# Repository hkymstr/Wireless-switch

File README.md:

# Wireless Race Car Switch System — Hardware v2 (WiFi)

A fully wireless switch panel for a race car using two **Raspberry Pi Pico 2 W** boards.  
One board acts as the **Transmitter** (switch panel), the other as the **Receiver** (12 V output driver).

> **Bluetooth version:** see the `bluetooth` branch.

---

## System Overview

```
 ┌──────────────────────────┐      WiFi (AP/STA)      ┌─────────────────────────────┐
 │      TRANSMITTER         │ ◄──── UDP 20 Hz ──────► │        RECEIVER             │
 │    Raspberry Pi Pico 2W  │                          │    Raspberry Pi Pico 2W     │
 │                          │  Web UI: 192.168.4.1     │  Web UI: <RX-IP>            │
 │  GPIO 1-5 ← 5 switches   │                          │  GPIO 8-11 → 4× MOSFET     │
 │  GPIO 0  → Connected LED │                          │  GPIO 12   → Relay K2      │
 │  GPIO 7  → Searching LED │                          │  GPIO 0    → Connected LED  │
 │  Powered from 12 V via   │                          │  GPIO 7    → Searching LED  │
 │  on-board 5 V regulator  │                          │  Takes 12 V from car        │
 └──────────────────────────┘                          └─────────────────────────────┘
```

TX creates an **open WiFi access point** (`WirelessSwitch-1` by default). RX connects as a station.  
Both boards host a **web settings page** — join the WiFi network and open a browser to configure.

---

## Web Interface

| Board | URL | What you can change |
|-------|-----|---------------------|
| TX | `http://192.168.4.1` | Pair ID |
| RX | `http://<RX-IP>` (linked from TX page) | Pair ID, hold time, channel modes |

Connect any phone or laptop to the `WirelessSwitch-N` WiFi network (no password), then open the URL above. Settings are saved to flash and survive power cycles.

---

## GPIO Pin Mapping — Hardware v2

### Status LEDs (identical on both boards)

| GPIO | Function      | Behaviour                                     |
|------|---------------|-----------------------------------------------|
|  0   | CONNECTED LED | Solid ON when wireless link is up             |
|  7   | SEARCHING LED | Flashes 2 Hz while searching; OFF when linked |

### Transmitter — Switch Inputs

Switches are **active-low** (connect switch between GPIO pin and GND).  
Internal pull-ups enabled in firmware.

| GPIO | Channel | Description    |
|------|---------|----------------|
|  1   | SW1     | Switch 1 input |
|  2   | SW2     | Switch 2 input |
|  3   | SW3     | Switch 3 input |
|  4   | SW4     | Switch 4 input |
|  5   | SW5     | Switch 5 input |

### Receiver — Output Channels

Outputs are **active-high** (GPIO HIGH = output energised).

| GPIO | Channel | Type            | Max Load         |
|------|---------|-----------------|------------------|
|  8   | CH1     | N-ch MOSFET     | 5 A @ 12 V       |
|  9   | CH2     | N-ch MOSFET     | 5 A @ 12 V       |
| 10   | CH3     | N-ch MOSFET     | 5 A @ 12 V       |
| 11   | CH4     | N-ch MOSFET     | 5 A @ 12 V       |
| 12   | CH5     | Relay K2 (SPDT) | Per relay rating |

---

## Repository Structure

```
├── kicad/
│   ├── wireless_switch.kicad_pro   KiCad project file
│   ├── wireless_switch.kicad_sch   Top-level schematic
│   ├── Pico_interface.kicad_sch    Pico 2 W GPIO interface sub-sheet
│   ├── analog_in.kicad_sch         Output channel sub-sheet (MOSFET + relay)
│   ├── input_power.kicad_sch       12 V → 5 V power supply sub-sheet
│   ├── wireless_switch.kicad_pcb   PCB layout
│   └── sym-lib-table               KiCad symbol library table
│
├── firmware/
│   ├── config.py        Shared configuration (defaults – overridden by web UI)
│   ├── tx_main.py       Transmitter MicroPython firmware
│   ├── rx_main.py       Receiver MicroPython firmware
│   ├── install_tx.bat   Windows transmitter installer  (default COM3)
│   ├── install_rx.bat   Windows receiver installer     (default COM5)
│   ├── install_tx.sh    Linux / macOS transmitter installer
│   ├── install_rx.sh    Linux / macOS receiver installer
│   ├── verify.bat       18-point verification script (Windows)
│   ├── led_test.bat     LED blink test (Windows)
│   └── polarity_test.bat  LED polarity / GPIO finder (Windows)
│
└── docs/
    └── wireless_switch.pdf   Full schematic PDF
```

---

## Hardware Requirements

### Per Board (× 2)
- Raspberry Pi Pico 2 W
- PCB from `kicad/wireless_switch.kicad_pcb`

### Transmitter PCB BOM additions
- 5× panel-mount toggle switches (SPDT or SPST)
- 2× LEDs with 330 Ω series resistors for GPIO 0 & 7
- 12 V → 5 V onboard regulator + capacitors (see `input_power.kicad_sch`)

### Receiver PCB BOM additions
- 4× N-channel logic-level MOSFETs (e.g. IRLZ44N) with gate resistors
- 1× 12 V SPDT relay K2 (Omron G5V-1 or equivalent)
- Relay driver transistor + flyback diodes
- Fusing on each output channel

---

## Software Installation

### Step 1 — Flash MicroPython to each Pico 2 W

1. Download the **Pico 2 W** MicroPython UF2 from  
   `https://micropython.org/download/RPI_PICO2_W/`
2. Hold **BOOTSEL**, plug USB → Pico appears as `RPI-RP2` mass storage
3. Drag the `.uf2` onto the drive — Pico reboots automatically

### Step 2 — Install `mpremote`

```bash
pip install mpremote
```

### Step 3 — Install Transmitter firmware

**Windows** (default COM3):
```bat
cd firmware
install_tx.bat
install_tx.bat COM4    ← specify a different port if needed
```

**Linux / macOS:**
```bash
cd firmware
chmod +x install_tx.sh && ./install_tx.sh
```

Confirm: board blinks SEARCHING LED **3× quickly** then flashes slowly.

### Step 4 — Install Receiver firmware

**Windows** (default COM5):
```bat
install_rx.bat
```

**Linux / macOS:**
```bash
./install_rx.sh
```

### Step 5 — Verify (optional, Windows)

```bat
verify.bat COM3 COM5
led_test.bat COM3 COM5
```

---

## Operation

1. **Power on both boards.** Both blink the SEARCHING LED **3× quickly** to confirm firmware is running.
2. TX creates an open WiFi access point. Both boards flash their SEARCHING LED while waiting for a link.
3. Once linked, **CONNECTED LED turns solid** on both boards; SEARCHING LED turns off.
4. Pressing a switch on TX activates the corresponding output on RX according to that channel's mode.
5. **On link loss:** RX holds its last output states for the configured hold time (default 10 s), then turns all outputs off. Both boards resume searching.

### Link Parameters

| Parameter           | Value                  |
|---------------------|------------------------|
| Update rate         | 20 Hz (every 50 ms)    |
| Link timeout        | 2 s                    |
| Hold on disconnect  | 10 s (configurable)    |
| Protocol            | UDP port 4210          |
| WiFi mode           | TX = AP, RX = Station  |
| Network             | Open (no password)     |

---

## Channel Modes

Each output channel can be set independently via the RX web interface:

| Mode      | Behaviour                                            |
|-----------|------------------------------------------------------|
| Momentary | Output ON while switch is held; OFF when released    |
| Latch     | First press turns output ON; next press turns it OFF |

Latch state is preserved through brief disconnects (within hold window).  
A disconnection longer than the hold time resets all latch states to OFF.

---

## Multiple Pairs

If two TX/RX pairs operate at the same time, each pair needs a unique **Pair ID** so they don't cross-connect.

Set the same Pair ID on both boards in a pair via the web interface:

| Pair | TX SSID         | RX connects to  |
|------|-----------------|-----------------|
|  1   | WirelessSwitch-1 | WirelessSwitch-1 |
|  2   | WirelessSwitch-2 | WirelessSwitch-2 |

**Procedure for changing Pair ID:**
1. Connect to the current WiFi network
2. Open RX settings → change Pair ID → Save (RX reboots, now looks for new SSID)
3. Open TX settings (192.168.4.1) → change Pair ID → Save (TX reboots with new SSID)
4. RX reconnects automatically

---

## Troubleshooting

| Symptom | Likely cause | Fix |
|---------|--------------|-----|
| No 3× startup blink | Firmware not installed | Re-run the installer; verify MicroPython UF2 was flashed first |
| SEARCHING LED never stops flashing | Wrong Pair ID or TX not powered | Check both boards have the same Pair ID; confirm TX SEARCHING LED is also flashing |
| TX AP has stale WPA2 password | Old security settings cached in chip | Firmware resets the AP before configuring — power-cycle TX |
| Can't open web interface | Not connected to WirelessSwitch-N WiFi | Join the WiFi network first (no password), then open the URL |
| RX web page not reachable | RX IP unknown | Open TX page (192.168.4.1) first — it shows a clickable link to the RX page |
| Outputs don't activate | Wrong firmware on board | Confirm TX has `tx_main.py` installed as `main.py` |
| Latch output stuck after reboot | Expected — latch state is in RAM only | Press the switch once to toggle off |
| `mpremote` cannot find device | Driver missing or wrong port | Run `python -m mpremote connect list` |
| Pico not detected as storage | Not holding BOOTSEL | Hold BOOTSEL before plugging USB |

---

## Protocol Reference

UDP packet format (7 bytes, TX → RX, port 4210):

```
Byte 0   : 0xAA  (start marker)
Byte 1   : Switch 1 state  (0 = open, 1 = pressed)
Byte 2   : Switch 2 state
Byte 3   : Switch 3 state
Byte 4   : Switch 4 state
Byte 5   : Switch 5 state
Byte 6   : Checksum  = (SW1+SW2+SW3+SW4+SW5) & 0xFF
```

RX → TX heartbeat: `b"RXHERE"` (6 bytes, every 50 ms) — tells TX the RX's IP address.

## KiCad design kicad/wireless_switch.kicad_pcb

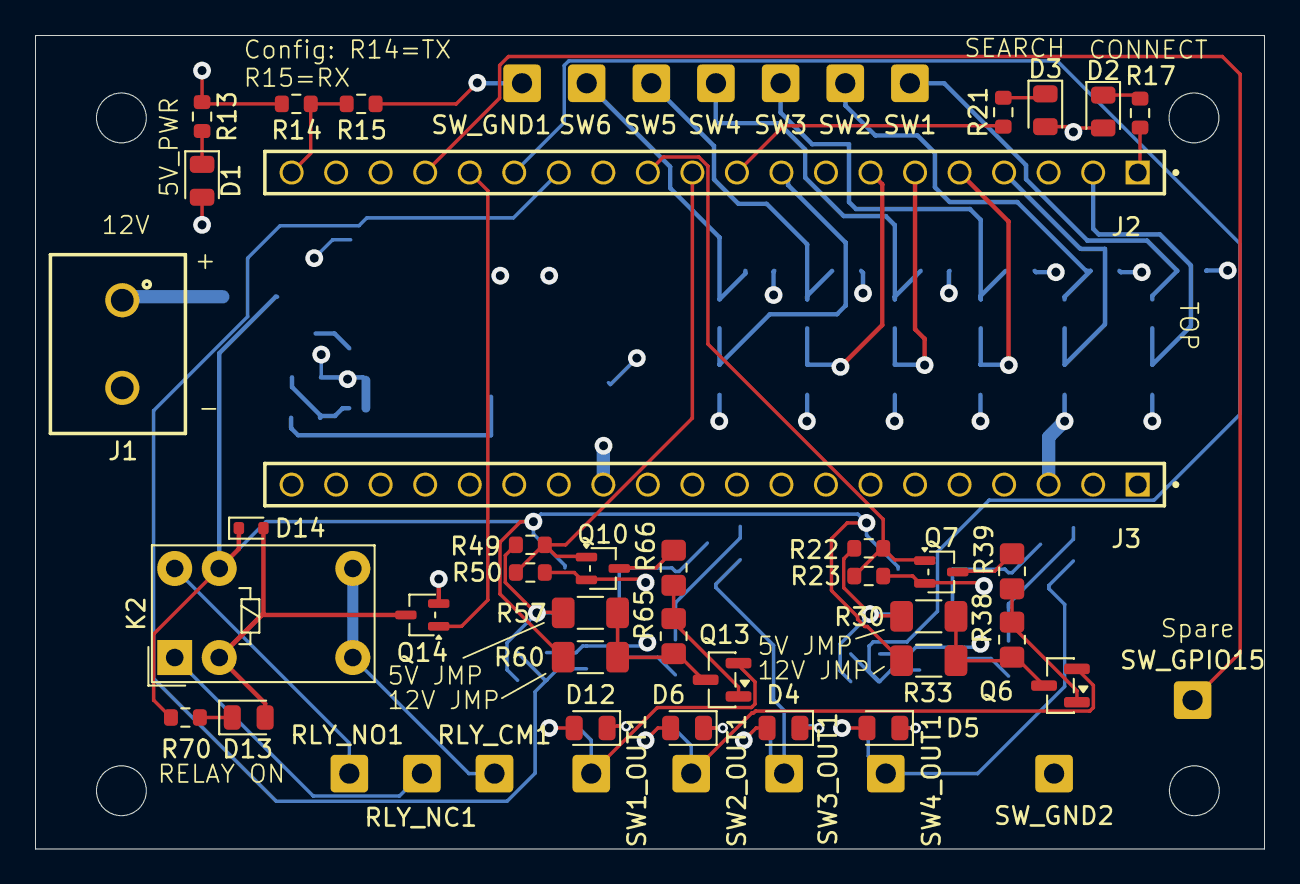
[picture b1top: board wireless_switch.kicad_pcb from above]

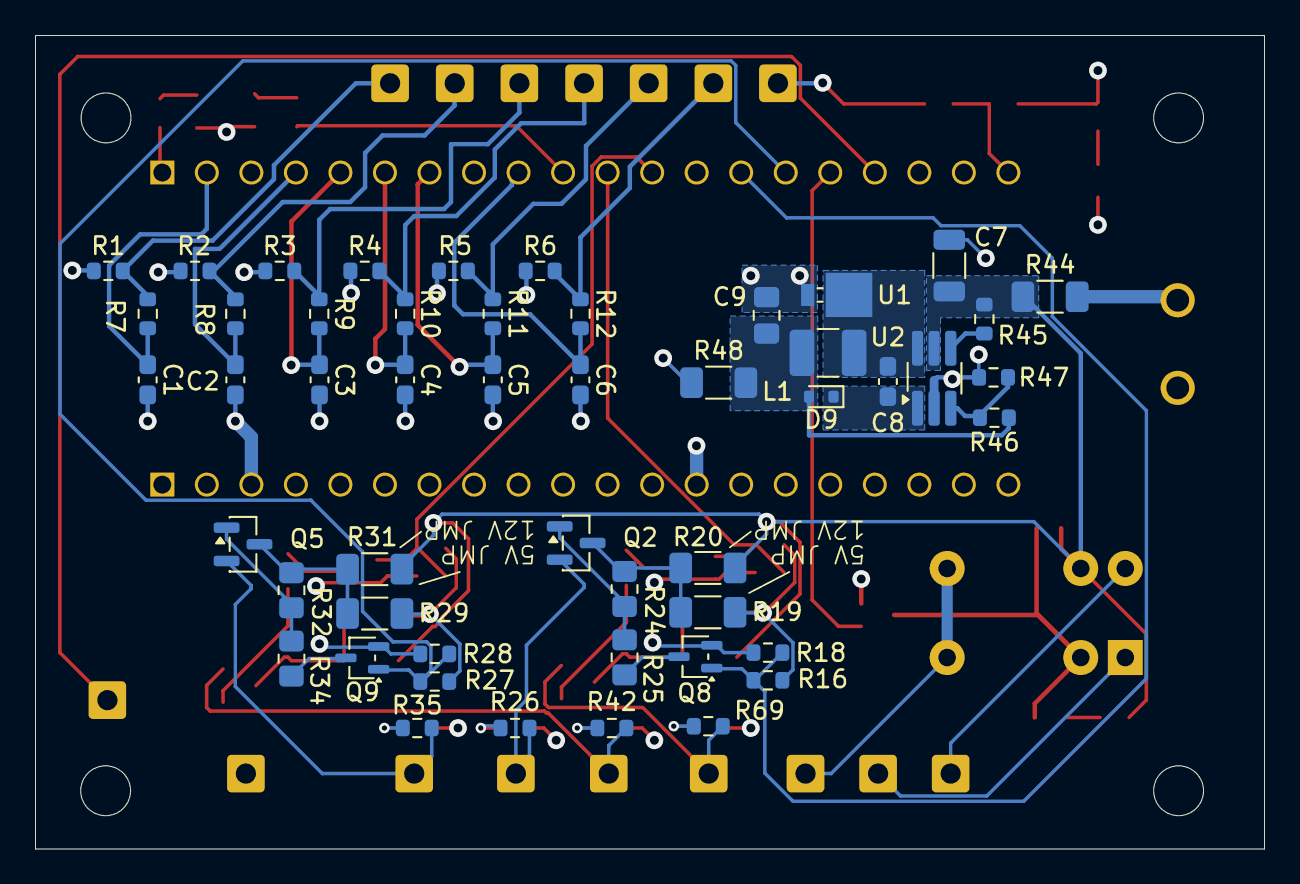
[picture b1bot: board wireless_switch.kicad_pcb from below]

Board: 4 copper layers, 70.1 x 46.4 mm, 102 parts (50 on the bottom side), 58 nets.

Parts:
C1, C2, C3, C4, C5, C6, C8: 0.1uF; C_0603_1608Metric_Pad1.08x0.95mm_HandSolder
C7: 2.2uF; C_1206_3216Metric
C9: 22uF; C_0805_2012Metric_Pad1.18x1.45mm_HandSolder
D1, D2, D3, D4, D5, D6, D12, D13: LTST-C171KGKT; LED_0805_2012Metric
D9, D14: 1N4148; D_SOD-523
J1: 691137710002
J2, J3: PPPC201LFBN-RC; SAMTEC_ESQ-120-24-G-S
K2: G5V-1; Relay_SPDT_Omron_G5V-1
L1: 22uH; L_1210_3225Metric_Pad1.42x2.65mm_HandSolder
Q2, Q5, Q6, Q13: MOSFET P-CH 30V; SOT-23
Q7, Q8, Q9, Q10: MOSTFET N-CH 50V; SOT-323_SC-70
Q14: Q_NMOS_GSD; SOT-323_SC-70
R1, R2, R3, R4, R5, R6, R13, R14, R15, R16, R17, R18, R21, R22, R23, R26, R27, R28, R35, R42, R45, R49, R50, R69, R70: 1k; R_0603_1608Metric
R7, R8, R9, R10, R11, R12, R47: 10k; R_0603_1608Metric
R19, R20, R29, R30, R31, R33, R44, R48, R57, R60: 50milli; R_1206_3216Metric_Pad1.30x1.75mm_HandSolder
R24, R25, R32, R34, R38, R39, R65, R66: 1k; R_0805_2012Metric_Pad1.20x1.40mm_HandSolder
R46: 30.1k; R_0603_1608Metric
RLY_CM1: RCT-0C; SolderWire-0.5sqmm_1x01_D0.9mm_OD2.1mm
RLY_NC1: RCT-0C; SolderWire-0.5sqmm_1x01_D0.9mm_OD2.1mm
RLY_NO1: RCT-0C; SolderWire-0.5sqmm_1x01_D0.9mm_OD2.1mm
SW1, SW1_OUT1, SW2, SW2_OUT1, SW3, SW3_OUT1, SW4, SW4_OUT1, SW5, SW6: RCT-0C; SolderWire-0.5sqmm_1x01_D0.9mm_OD2.1mm
SW_GND1, SW_GND2: RCT-0C; SolderWire-0.5sqmm_1x01_D0.9mm_OD2.1mm
SW_GPIO15: RCT-0C; SolderWire-0.5sqmm_1x01_D0.9mm_OD2.1mm
U1: MBRM140T3G; D_Powermite_AK
U2: LT1933IS6_TRPBF; TSOT-23-6_HandSoldering

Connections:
/5V: R1.1, R2.1, R3.1, R4.1, R5.1, R6.1, R13.1, R14.1, R16.1, R19.1, R22.1, R27.1, R29.1, R30.1, R48.1, R49.1, R57.1
/12V_FILT: C7.1, D14.1 (K), K2.9, R20.1, R31.1, R33.1, R44.1, R45.2, R60.1, R70.1, U2.5 (VIN)
/CONNECTED: J2.01, R17.1
/GPIO1: C1.1, J2.02, R7.2
/GPIO2: C2.1, J2.04, R8.2
/GPIO3: C3.1, J2.05, R9.2
/GPIO4: C4.1, J2.06, R10.2
/GPIO5: C5.1, J2.07, R11.2
/GPIO6: C6.1, J2.09, R12.2
/GPIO7: J2.10, R21.1
/GPIO8: J2.11, Q10.1 (G), R49.2, R50.1
/GPIO9: J2.12, Q7.1 (G), R22.2, R23.1
/GPIO10: J2.14, Q8.1 (G), R16.2, R18.1
/GPIO11: J2.15, Q9.1 (G), R27.2, R28.1
/GPIO12: J2.16, Q14.1 (G)
/GPIO13: J2.17, SW_GPIO15.1
/GPIO15: J2.20, R14.2, R15.1
/Input_Power/BOOST: C8.1, D9.1 (K), U2.1 (BOOST)
/Input_Power/V_IN: J1.1, R44.2
/OUTPUT_CIRCUIT1/OUT1+: Q6.2 (S), R42.1, SW2_OUT1.1
/OUTPUT_CIRCUIT2/OUT1+: Q2.2 (S), R26.1, SW3_OUT1.1
/OUTPUT_CIRCUIT3/OUT1+: Q5.2 (S), R35.1, SW4_OUT1.1
/OUTPUT_CIRCUIT/OUT1+: Q13.2 (S), R69.1, SW1_OUT1.1
/RELAY_GND: D13.2, D14.2 (A), K2.2, Q14.3 (D)
GND: C1.2, C2.2, C3.2, C4.2, C5.2, C6.2, C7.2, C9.2, D1.2, D2.2, D3.2, D4.2, D5.2, D6.2, D12.2, J1.2, J2.03, J2.08, J2.13, J2.18, J3.03, J3.13, J3.18, Q7.2 (S), Q8.2 (S), Q9.2 (S), Q10.2 (S), Q14.2 (S), R15.2, R18.2, R23.2, R28.2, R47.2, R50.2, SW_GND1.1, SW_GND2.1, U1.2, U2.2 (GND)
unnamed: D1.1, R13.2
unnamed: D2.1, R17.2
unnamed: D3.1, R21.2
unnamed: D4.1, R26.2
unnamed: D5.1, R35.2
unnamed: D6.1, R42.2
unnamed: C9.1, D9.2 (A), L1.2, R46.1, R48.2
unnamed: D12.1, R69.2
unnamed: D13.1, R70.2
unnamed: K2.1, RLY_NC1.1
unnamed: K2.5, K2.6, RLY_CM1.1
unnamed: K2.10, RLY_NO1.1
unnamed: Q2.3 (D), R19.2, R20.2, R24.2
unnamed: Q2.1 (G), R24.1, R25.2
unnamed: Q5.3 (D), R29.2, R31.2, R32.2
unnamed: Q5.1 (G), R32.1, R34.2
unnamed: Q6.3 (D), R30.2, R33.2, R38.2
unnamed: Q6.1 (G), R38.1, R39.2
unnamed: Q7.3 (D), R39.1
unnamed: Q8.3 (D), R25.1
unnamed: Q9.3 (D), R34.1
unnamed: Q10.3 (D), R66.1
unnamed: Q13.3 (D), R57.2, R60.2, R65.2
unnamed: Q13.1 (G), R65.1, R66.2
unnamed: R1.2, R7.1, SW1.1
unnamed: R2.2, R8.1, SW2.1
unnamed: R3.2, R9.1, SW3.1
unnamed: R4.2, R10.1, SW4.1
unnamed: R5.2, R11.1, SW5.1
unnamed: R6.2, R12.1, SW6.1
unnamed: R45.1, U2.4 (*SHDN)
unnamed: R46.2, R47.1, U2.3 (FB)
unnamed: C8.2, L1.1, U1.1, U2.6 (SW)

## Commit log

2026-04-20 Add files via upload
    Kicad files for PWB that went to fab
2026-05-03 Add hardware-v2 branch: GPIO reassignment + firmware + docs
    KiCad schematic (based on existing wireless_switch design):
    - Added GPIO mapping annotation to top-level schematic
    - GPIO 0 : CONNECTED LED (both TX and RX)
    - GPIO 7 : SEARCHING LED - flashes while searching, OFF when linked
    - GPIO 1-5: Transmitter switch inputs (active-low)
    - GPIO 8-11: Receiver MOSFET outputs CH1-CH4 (5 A each)
2026-05-03 Add .gitignore for extracted design dir and KiCad artifacts
    https://claude.ai/code/session_016QqQ78B9vQB467ZraMVFxw
2026-05-03 Add Windows batch scripts for install and verification (COM3/COM5)
    - install_tx.bat : installs TX firmware, defaults to COM3
    - install_rx.bat : installs RX firmware, defaults to COM5
    - verify.bat : end-to-end check of both devices - tests MicroPython,
    config, GPIO init, LED toggles, output channel pulses,
    and WiFi chip presence on TX (COM3) and RX (COM5)
    https://claude.ai/code/session_016QqQ78B9vQB467ZraMVFxw
2026-05-03 Fix verify.bat: pulse test and results block syntax
    - Replace p.__setattr__('value',1) with p.on()/p.off() for output pulse test
    - Fix 'unexpected token' error in results block by replacing if/else with
    goto labels and escaping parentheses in echo statements
    https://claude.ai/code/session_016QqQ78B9vQB467ZraMVFxw
2026-05-03 Add LED visibility and polarity test scripts
    - led_test.bat : blinks GPIO 0 and GPIO 7 on both boards simultaneously,
    10 x 500ms flashes so they are clearly visible
    - polarity_test.bat: interactive test to determine active-high vs active-low
    wiring and locate the actual GPIO if it differs from config
    https://claude.ai/code/session_016QqQ78B9vQB467ZraMVFxw
2026-05-03 Fix TX AP SSID not being applied on boot
    ap.config() must be called before ap.active(True), not after.
    Activating the AP first causes MicroPython to use the default
    board SSID (PICOFA2C). Also use authmode=3 integer directly
    to avoid any AUTH_WPA2_PSK constant lookup issues.
    https://claude.ai/code/session_016QqQ78B9vQB467ZraMVFxw
2026-05-03 Fix RX searching LED staying ON after WiFi connect; clean up LED logic
    - Remove incorrect active-low LED_ON/LED_OFF constants (LEDs are active-high)
    - Fix last_rx_time init bug: was set to now() causing link_ok=True on first
    tick before any UDP packet received, leaving searching LED in wrong state.
    Now initialised LINK_TIMEOUT_MS in the past so RX starts in searching state
    and only transitions to connected when a real packet arrives from TX.
    - Replace search_led_state bool toggle with searching_led.toggle() in both
2026-05-03 Fix TX LEDs never lighting; add startup blink and crash handler
    - Remove ap.active(False) before ap.config() - caused silent exception on
    Pico W MicroPython v1.27 which killed firmware before any LED code ran
    - Blink searching LED 3x immediately at startup so user can confirm
    firmware is running before WiFi init
    - Flash searching LED during AP startup instead of after
    - Add blink_error() fast-flash pattern for fatal errors
2026-05-03 Fix RX WiFi never connecting; add startup blink and crash handler
    - connect_wifi() was calling sta.connect() every 500ms in a loop, constantly
    interrupting its own connection handshake. Now calls connect() once then
    waits up to 30 seconds for sta.isconnected() to become True.
    - Add 3-blink startup confirmation (same as TX) so user can see firmware running
    - Add 30 s WiFi timeout returning None so caller can signal error via blink_error()
    - Add blink_error() fast-flash for fatal crashes
2026-05-03 Switch to open WiFi network (no password)
    The security= parameter in ap.config() was silently ignored by the cyw43
    driver on MicroPython v1.27, leaving the AP open. The RX and phone were
    both trying to authenticate against an open AP, causing connection failure.
    Open network is appropriate for a race car - no authentication overhead,
    faster reconnect, shorter range means no external interference risk.
    https://claude.ai/code/session_016QqQ78B9vQB467ZraMVFxw
2026-05-03 Force AP to open: deactivate before config to clear old WPA2 password
    The Pico W WiFi chip retains previous security settings across reboots.
    Without ap.active(False) first, ap.config(security=0) had no effect and
    the AP kept broadcasting with WPA2 requiring the old password.
    Fix: wrap ap.active(False) in try/except so it can't crash the firmware,
    then explicitly set security=0 and password='' before reactivating.
    Also: RX connect_wifi() now retries sta.connect() every 5 s with a 60 s
2026-05-03 Switch transport from WiFi/UDP to Bluetooth BLE (GATT notify)
    TX becomes a BLE peripheral: advertises WirelessSwitch-TX, exposes a
    notify characteristic, pushes 7-byte switch packet at 20 Hz.
    RX becomes a BLE central: scans for the device name, connects, subscribes
    to the characteristic, applies received states to outputs.
    config.py replaces WiFi/UDP settings with BT_DEVICE_NAME and 128-bit UUIDs.
    https://claude.ai/code/session_016QqQ78B9vQB467ZraMVFxw
2026-05-04 Fix BLE advertisement payload exceeding 31-byte limit
    Removed UUID128 from advertisement (flags+name+UUID128 = 39 bytes, over limit).
    Now advertises flags + complete local name only (21 bytes).
    RX scans indefinitely (duration=0) and restarts automatically if scan ends
    without finding TX. Added debug prints for serial monitoring.
    https://claude.ai/code/session_016QqQ78B9vQB467ZraMVFxw
2026-05-04 Fix disconnect loop: defer BLE calls from IRQ, wait for CCCD before notifying
    TX now waits for RX to write CCCD before sending any gatts_notify calls.
    This prevents TX notifications from flooding the ATT channel during GATT
    service/characteristic discovery, which was causing the CCCD write to fail
    and RX to immediately disconnect.
    Both sides now use flags (do_advertise, do_scan, do_connect) to defer
    gap_advertise/gap_scan/gap_connect out of IRQ handlers into the main loop,
2026-05-04 Simplify BLE: remove GATT discovery and CCCD dependency
    TX no longer waits for CCCD write (which may not trigger _IRQ_GATTS_WRITE
    in all MicroPython builds). Instead adds a 1-second settle delay after
    connect before sending the first notification, giving RX time to stabilise.
    RX drops all GATT service/characteristic discovery. Connects and passively
    waits for _IRQ_GATTC_NOTIFY. Eliminates the gattc_write-to-CCCD call that
    was the most likely cause of the immediate disconnect.
2026-05-04 Add hold-on-disconnect (10 s) and per-channel momentary/latch modes
    On link loss, outputs now hold their last state for HOLD_ON_DISCONNECT_MS
    (10 s) before releasing. This allows brief signal dropouts in the race car
    without killing power to active channels.
    CHANNEL_MODES in config.py sets each channel independently:
    MODE_MOMENTARY: output follows switch (current behaviour)
    MODE_LATCH: each button press toggles output ON/OFF (rising edge)
2026-05-04 Update README: open WiFi network, Windows installers, startup blink behaviour
    https://claude.ai/code/session_016QqQ78B9vQB467ZraMVFxw
2026-05-04 Rewrite README for Bluetooth branch
    Replaces WiFi-centric README with accurate BLE documentation:
    - BLE transport overview (peripheral/central roles, GATT notify)
    - Channel modes (momentary / latch) with config example
    - Hold-on-disconnect behaviour (10 s before outputs release)
    - Windows and Linux/macOS install instructions
    - Phone monitoring via nRF Connect / LightBlue
2026-05-05 Add PAIR_ID to config for multi-pair isolation
    PAIR_ID is a single integer in config.py. BT_DEVICE_NAME is derived from it
    ("WirelessSwitch-1", "WirelessSwitch-2", etc.) so each TX/RX pair advertises
    and scans for a unique name. Set the same PAIR_ID on both boards in a pair
    before flashing. Different pairs in range cannot cross-connect.
    README updated with Step 6 explaining multi-pair setup.
    https://claude.ai/code/session_016QqQ78B9vQB467ZraMVFxw
2026-05-05 Add web UI, hold-on-disconnect, latch modes, and PAIR_ID to WiFi branch
    Web interface (HTTP port 80):
    TX: http://192.168.4.1 -- shows switch states, link status, PAIR_ID form
    RX: http://<RX-IP> -- shows output states, hold time, channel mode selects
    TX page links directly to RX page when connected.
    Settings saved to user_config.json on flash; persist across reboots.
    PAIR_ID isolates multiple TX/RX pairs. WIFI_SSID derived as
2026-05-06 Fix RX reconnect, POST body parsing, and add TX back-link
    - Reconnect: limit WiFi retry to every 5 s with interface reset
    (active False/True) so TX power-cycle triggers clean reconnect
    - POST body: do a second recv() when body is missing from first
    packet, fixing settings not saving on most browsers
    - Web UI: add back-link to http://192.168.4.1/ on RX settings page
    https://claude.ai/code/session_016QqQ78B9vQB467ZraMVFxw
2026-05-06 Add firmware version to config and web UI footer
    Version 2.1.0 shown at bottom of both TX and RX settings pages.
    Bump version in config.py for future reference.
    https://claude.ai/code/session_016QqQ78B9vQB467ZraMVFxw
